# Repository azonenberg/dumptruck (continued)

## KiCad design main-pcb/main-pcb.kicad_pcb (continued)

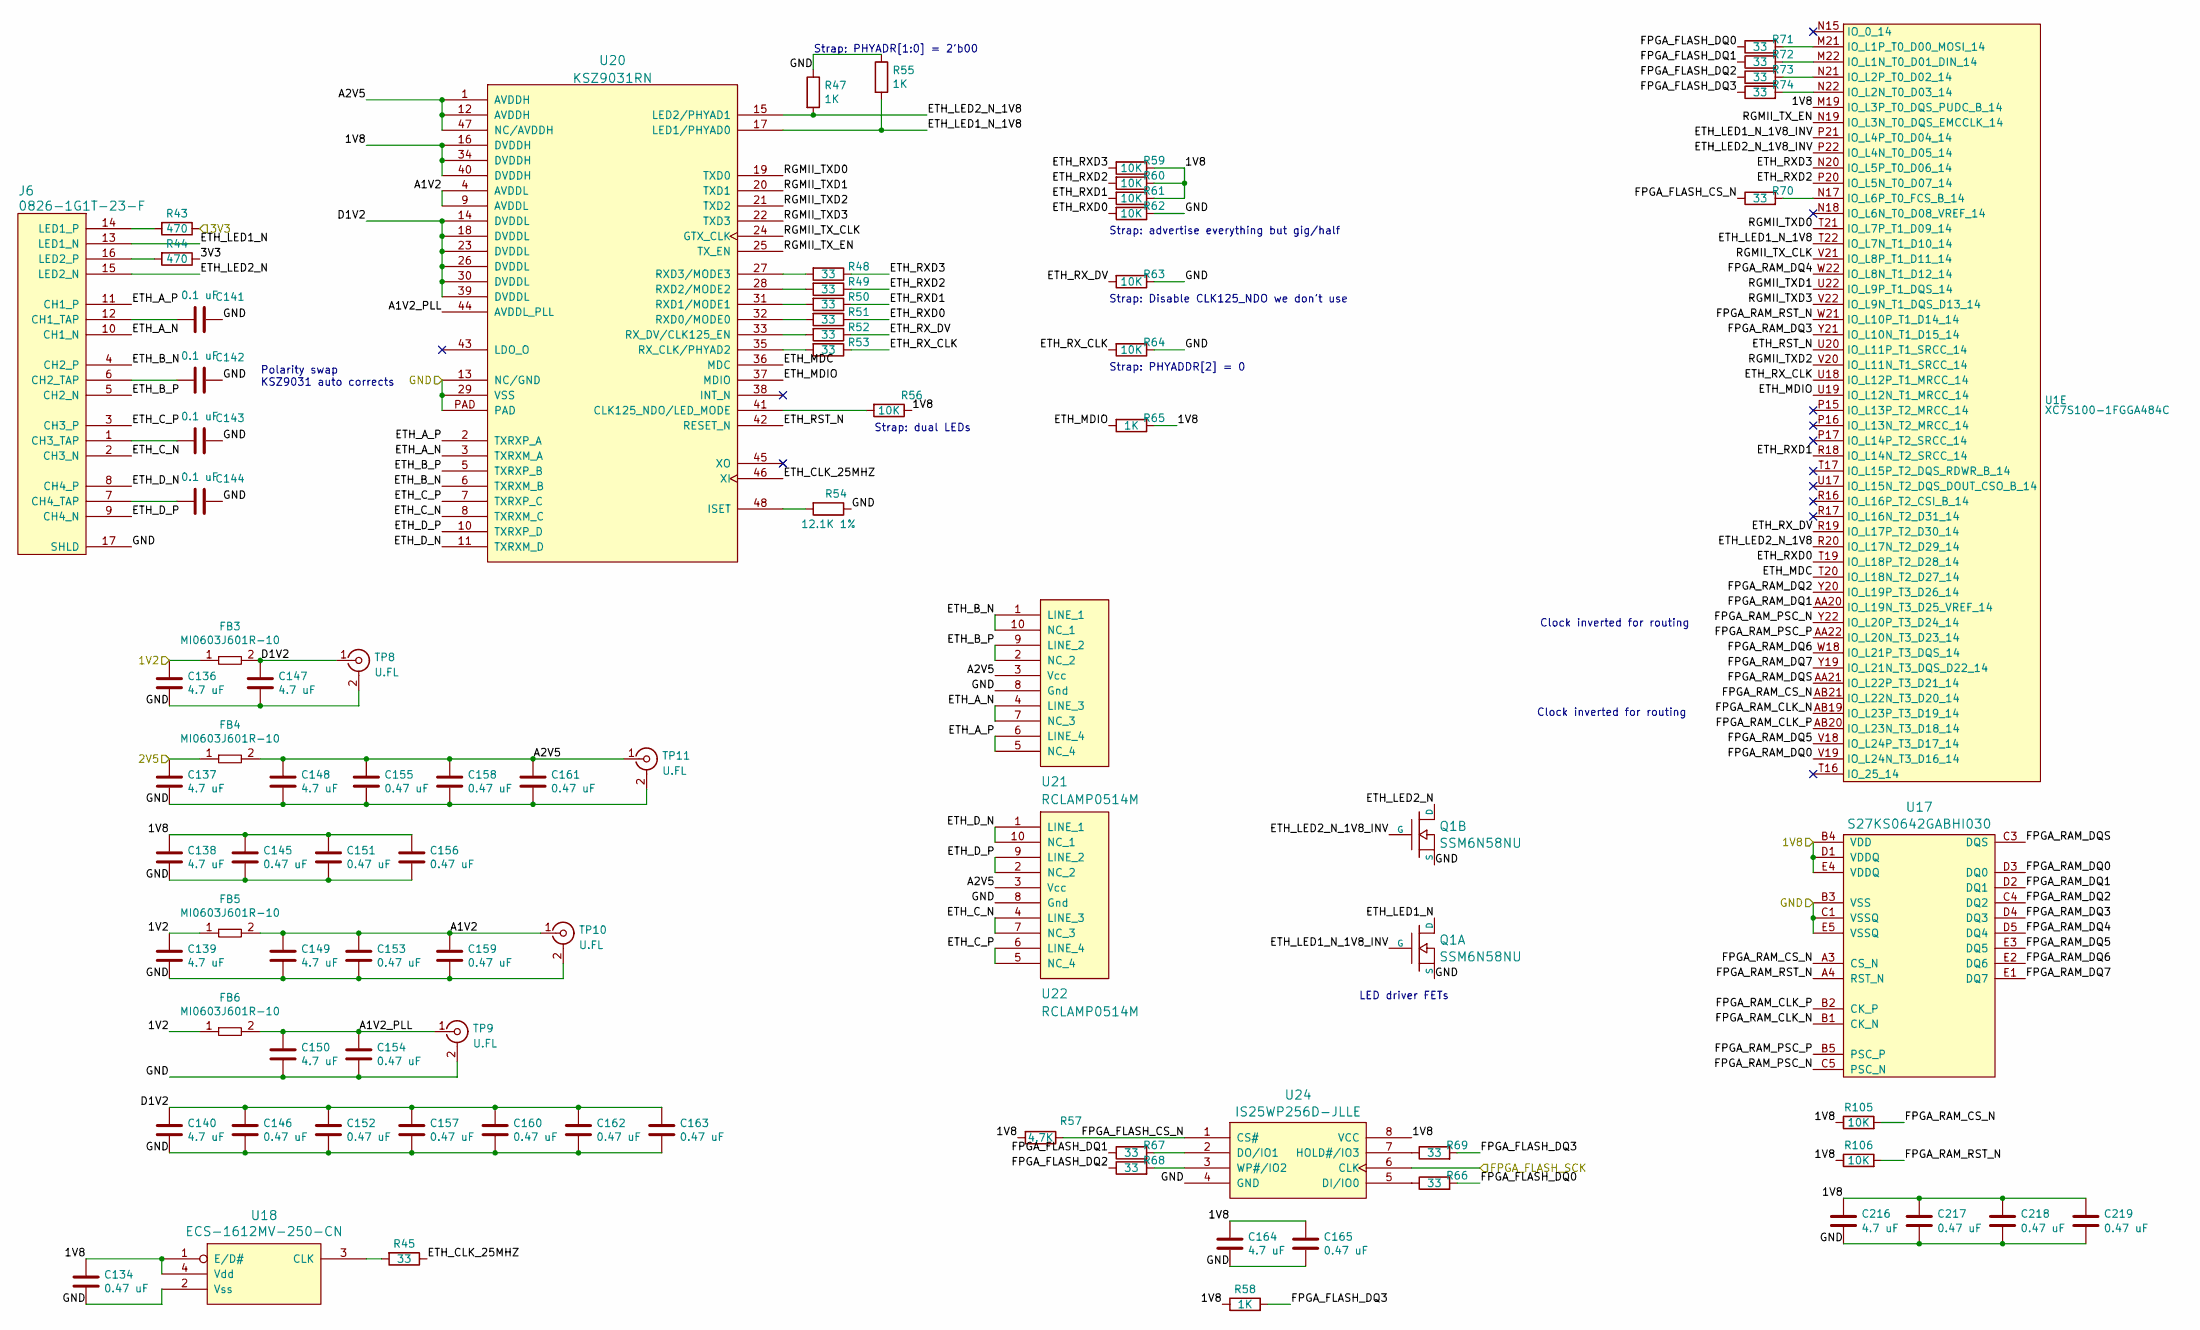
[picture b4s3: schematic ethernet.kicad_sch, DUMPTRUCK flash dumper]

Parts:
C134, C145, C146, C151, C152, C153, C154, C155, C156, C157, C158, C159, C160, C161, C162, C163, C165, C217, C218, C219: 0.47 uF; EIA_0402_CAP_NOSILK
C136, C137, C138, C139, C140, C147, C148, C149, C150, C164, C216: 4.7 uF; EIA_0603_CAP_NOSILK
C141, C142, C143, C144: 0.1 uF; EIA_0402_CAP_NOSILK
FB3, FB4, FB5, FB6: MI0603J601R-10; EIA_0603_INDUCTOR_NOSILK
J6: 0826-1G1T-23-F; CONN_BELFUSE_0826_1G1T_23_F
Q1: SSM6N58NU; DFN_6_0.65MM_2x2MM_GDS
R43, R44: 470; EIA_0402_RES_NOSILK
R45, R48, R49, R50, R51, R52, R53, R66, R67, R68, R69, R70, R71, R72, R73, R74: 33; EIA_0402_RES_NOSILK
R47, R55, R58, R65: 1K; EIA_0402_RES_NOSILK
R54: 12.1K 1%; EIA_0402_RES_NOSILK
R56, R59, R60, R61, R62, R63, R64, R105, R106: 10K; EIA_0402_RES_NOSILK
R57: 4.7K; EIA_0402_RES_NOSILK
TP8, TP9, TP10, TP11: U.FL; CONN_U.FL_TE_1909763-1
U1: XC7S100-1FGGA484C; BGA_484_22x22_FULLARRAY_1MM
U17: S27KS0642GABHI030; BGA_24_6x8_DEPOP1_1MM
U18: ECS-1612MV-250-CN; OSCILLATOR_1.6x1.2
U20: KSZ9031RN; QFN_48_0.5MM_7x7MM
U21, U22: RCLAMP0514M; SOP_10_0.5MM_3MM
U24: IS25WP256D-JLLE; DFN_8_1.27MM_8x6MM

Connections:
/1V2: C136.1, C139.1, FB3.1, FB5.1, FB6.1; also elsewhere on the board
/1V8: C134.1, C138.1, C145.1, C151.1, C156.1, C164.1, C165.1, C216.1, C217.1, C218.1, C219.1, R56.1, R57.2, R58.1, R59.1, R60.1, R61.1, R65.1, R105.1, R106.1, U1.M19 (IO_L3P_T0_DQS_PUDC_B_14), U17.B4 (VDD), U17.D1 (VDDQ), U17.E4 (VDDQ), U18.1 (E/D#), U18.4 (Vdd), U20.16 (DVDDH), U20.34 (DVDDH), U20.40 (DVDDH), U24.8 (VCC); also elsewhere on the board
/2V5: C137.1, FB4.1; also elsewhere on the board
/3V3: R43.1, R44.1; also elsewhere on the board
/Ethernet/A1V2: C149.1, C153.1, C159.1, FB5.2, TP10.1 (In), U20.4 (AVDDL), U20.9 (AVDDL)
/Ethernet/A1V2_PLL: C150.1, C154.1, FB6.2, TP9.1 (In), U20.44 (AVDDL_PLL)
/Ethernet/A2V5: C148.1, C155.1, C158.1, C161.1, FB4.2, TP11.1 (In), U20.1 (AVDDH), U20.12 (AVDDH), U20.47 (NC/AVDDH), U21.3 (Vcc), U22.3 (Vcc)
/Ethernet/D1V2: C140.1, C146.1, C147.1, C152.1, C157.1, C160.1, C162.1, C163.1, FB3.2, TP8.1 (In), U20.14 (DVDDL), U20.18 (DVDDL), U20.23 (DVDDL), U20.26 (DVDDL), U20.30 (DVDDL), U20.39 (DVDDL)
/Ethernet/ETH_A_N: J6.10 (CH1_N), U20.3 (TXRXM_A), U21.4 (LINE_3), U21.7 (NC_3)
/Ethernet/ETH_A_P: J6.11 (CH1_P), U20.2 (TXRXP_A), U21.5 (NC_4), U21.6 (LINE_4)
/Ethernet/ETH_B_N: J6.4 (CH2_P), U20.6 (TXRXM_B), U21.1 (LINE_1), U21.10 (NC_1)
/Ethernet/ETH_B_P: J6.5 (CH2_N), U20.5 (TXRXP_B), U21.2 (NC_2), U21.9 (LINE_2)
/Ethernet/ETH_CLK_25MHZ: R45.1, U20.46 (XI)
/Ethernet/ETH_C_N: J6.2 (CH3_N), U20.8 (TXRXM_C), U22.4 (LINE_3), U22.7 (NC_3)
/Ethernet/ETH_C_P: J6.3 (CH3_P), U20.7 (TXRXP_C), U22.5 (NC_4), U22.6 (LINE_4)
/Ethernet/ETH_D_N: J6.8 (CH4_P), U20.11 (TXRXM_D), U22.1 (LINE_1), U22.10 (NC_1)
/Ethernet/ETH_D_P: J6.9 (CH4_N), U20.10 (TXRXP_D), U22.2 (NC_2), U22.9 (LINE_2)
/Ethernet/ETH_LED1_N: J6.13 (LED1_N), Q1.D1 (D)
/Ethernet/ETH_LED1_N_1V8: R55.2, U1.T22 (IO_L7N_T1_D10_14), U20.17 (LED1/PHYAD0)
/Ethernet/ETH_LED1_N_1V8_INV: Q1.G1 (G), U1.P21 (IO_L4P_T0_D04_14)
/Ethernet/ETH_LED2_N: J6.15 (LED2_N), Q1.D2 (D)
/Ethernet/ETH_LED2_N_1V8: R47.2, U1.R20 (IO_L17N_T2_D29_14), U20.15 (LED2/PHYAD1)
/Ethernet/ETH_LED2_N_1V8_INV: Q1.G2 (G), U1.P22 (IO_L4N_T0_D05_14)
/Ethernet/ETH_MDC: U1.T20 (IO_L18N_T2_D27_14), U20.36 (MDC)
/Ethernet/ETH_MDIO: R65.2, U1.U19 (IO_L12N_T1_MRCC_14), U20.37 (MDIO)
/Ethernet/ETH_RST_N: U1.U20 (IO_L11P_T1_SRCC_14), U20.42 (RESET_N)
/Ethernet/ETH_RXD0: R51.1, R62.2, U1.T19 (IO_L18P_T2_D28_14)
/Ethernet/ETH_RXD1: R50.1, R61.2, U1.R18 (IO_L14N_T2_SRCC_14)
/Ethernet/ETH_RXD2: R49.1, R60.2, U1.P20 (IO_L5N_T0_D07_14)
/Ethernet/ETH_RXD3: R48.1, R59.2, U1.N20 (IO_L5P_T0_D06_14)
/Ethernet/ETH_RX_CLK: R53.1, R64.2, U1.U18 (IO_L12P_T1_MRCC_14)
/Ethernet/ETH_RX_DV: R52.1, R63.2, U1.R19 (IO_L17P_T2_D30_14)
/Ethernet/FPGA_FLASH_CS_N: R57.1, R70.1, U24.1 (CS#)
/Ethernet/FPGA_FLASH_DQ0: R66.2, R71.1
/Ethernet/FPGA_FLASH_DQ1: R67.1, R72.1
/Ethernet/FPGA_FLASH_DQ2: R68.1, R73.1
/Ethernet/FPGA_FLASH_DQ3: R58.2, R69.2, R74.1
/Ethernet/FPGA_RAM_CLK_N: U1.AB19 (IO_L23P_T3_D19_14), U17.B1 (CK_N)
/Ethernet/FPGA_RAM_CLK_P: U1.AB20 (IO_L23N_T3_D18_14), U17.B2 (CK_P)
/Ethernet/FPGA_RAM_CS_N: R105.2, U1.AB21 (IO_L22N_T3_D20_14), U17.A3 (CS_N)
/Ethernet/FPGA_RAM_DQ0: U1.V19 (IO_L24N_T3_D16_14), U17.D3 (DQ0)
/Ethernet/FPGA_RAM_DQ1: U1.AA20 (IO_L19N_T3_D25_VREF_14), U17.D2 (DQ1)
/Ethernet/FPGA_RAM_DQ2: U1.Y20 (IO_L19P_T3_D26_14), U17.C4 (DQ2)
/Ethernet/FPGA_RAM_DQ3: U1.Y21 (IO_L10N_T1_D15_14), U17.D4 (DQ3)
/Ethernet/FPGA_RAM_DQ4: U1.W22 (IO_L8N_T1_D12_14), U17.D5 (DQ4)
/Ethernet/FPGA_RAM_DQ5: U1.V18 (IO_L24P_T3_D17_14), U17.E3 (DQ5)
/Ethernet/FPGA_RAM_DQ6: U1.W18 (IO_L21P_T3_DQS_14), U17.E2 (DQ6)
/Ethernet/FPGA_RAM_DQ7: U1.Y19 (IO_L21N_T3_DQS_D22_14), U17.E1 (DQ7)
/Ethernet/FPGA_RAM_DQS: U1.AA21 (IO_L22P_T3_D21_14), U17.C3 (DQS)
/Ethernet/FPGA_RAM_PSC_N: U1.Y22 (IO_L20P_T3_D24_14), U17.C5 (PSC_N)
/Ethernet/FPGA_RAM_PSC_P: U1.AA22 (IO_L20N_T3_D23_14), U17.B5 (PSC_P)
/Ethernet/FPGA_RAM_RST_N: R106.2, U1.W21 (IO_L10P_T1_D14_14), U17.A4 (RST_N)
/Ethernet/RGMII_TXD0: U1.T21 (IO_L7P_T1_D09_14), U20.19 (TXD0)
/Ethernet/RGMII_TXD1: U1.U22 (IO_L9P_T1_DQS_14), U20.20 (TXD1)
/Ethernet/RGMII_TXD2: U1.V20 (IO_L11N_T1_SRCC_14), U20.21 (TXD2)
/Ethernet/RGMII_TXD3: U1.V22 (IO_L9N_T1_DQS_D13_14), U20.22 (TXD3)
/Ethernet/RGMII_TX_CLK: U1.V21 (IO_L8P_T1_D11_14), U20.24 (GTX_CLK)
/Ethernet/RGMII_TX_EN: U1.N19 (IO_L3N_T0_DQS_EMCCLK_14), U20.25 (TX_EN)
/FLASH_SCK: U24.6 (CLK); also elsewhere on the board
/GND: C134.2, C136.2, C137.2, C138.2, C139.2, C140.2, C141.1, C142.1, C143.1, C144.1, C145.2, C146.2, C147.2, C148.2, C149.2, C150.2, C151.2, C152.2, C153.2, C154.2, C155.2, C156.2, C157.2, C158.2, C159.2, C160.2, C161.2, C162.2, C163.2, C164.2, C165.2, C216.2, C217.2, C218.2, C219.2, J6.17 (SHLD), Q1.S1 (S), Q1.S2 (S), R47.1, R54.1, R55.1, R62.1, R63.1, R64.1, TP8.2 (Ext), TP9.2 (Ext), TP10.2 (Ext), TP11.2 (Ext), U17.B3 (VSS), U17.C1 (VSSQ), U17.E5 (VSSQ), U18.2 (Vss), U20.13 (NC/GND), U20.29 (VSS), U20.PAD, U21.8 (Gnd), U22.8 (Gnd), U24.4 (GND); also elsewhere on the board
unnamed: C141.2, J6.12 (CH1_TAP)
unnamed: C142.2, J6.6 (CH2_TAP)
unnamed: C143.2, J6.1 (CH3_TAP)
unnamed: C144.2, J6.7 (CH4_TAP)
unnamed: J6.14 (LED1_P), R43.2
unnamed: J6.16 (LED2_P), R44.2
unnamed: R72.2, U1.M22 (IO_L1N_T0_D01_DIN_14)
unnamed: R71.2, U1.M21 (IO_L1P_T0_D00_MOSI_14)
unnamed: R74.2, U1.N22 (IO_L2N_T0_D03_14)
unnamed: R73.2, U1.N21 (IO_L2P_T0_D02_14)
unnamed: R70.2, U1.N17 (IO_L6P_T0_FCS_B_14)
unnamed: R45.2, U18.3 (CLK)
unnamed: R56.2, U20.41 (CLK125_NDO/LED_MODE)
unnamed: R54.2, U20.48 (ISET)
unnamed: R51.2, U20.32 (RXD0/MODE0)
unnamed: R50.2, U20.31 (RXD1/MODE1)
unnamed: R49.2, U20.28 (RXD2/MODE2)
unnamed: R48.2, U20.27 (RXD3/MODE3)
unnamed: R53.2, U20.35 (RX_CLK/PHYAD2)
unnamed: R52.2, U20.33 (RX_DV/CLK125_EN)
unnamed: R66.1, U24.5 (DI/IO0)
unnamed: R67.2, U24.2 (DO/IO1)
unnamed: R69.1, U24.7 (HOLD#/IO3)
unnamed: R68.2, U24.3 (WP#/IO2)

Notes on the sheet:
Strap: Disable CLK125_NDO we don't use
Strap: dual LEDs
Strap: PHYADDR[2] = 0
LED driver FETs
Polarity swap KSZ9031 auto corrects
Strap: advertise everything but gig/half
Clock inverted for routing
Strap: PHYADR[1:0] = 2'b00

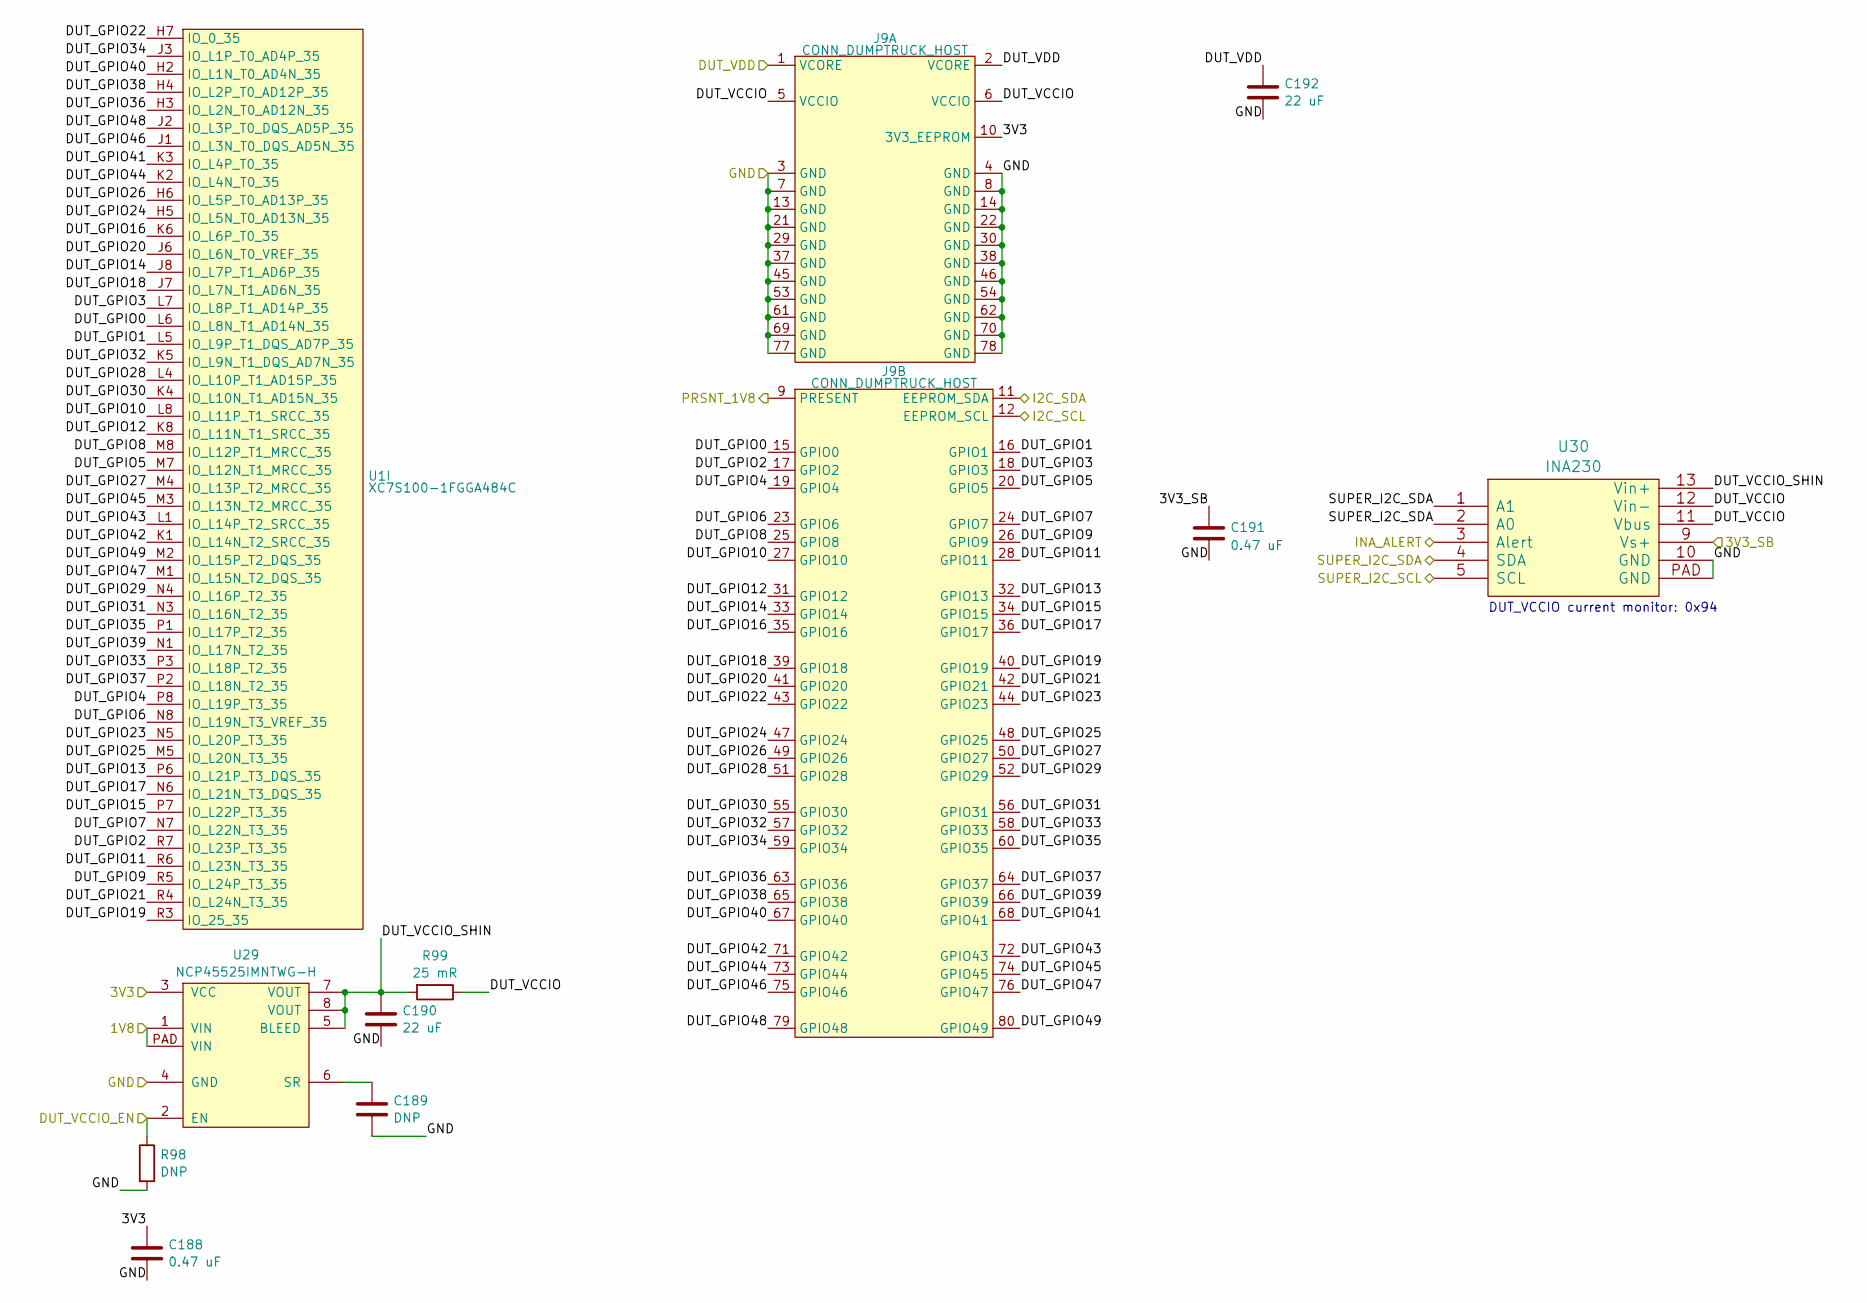
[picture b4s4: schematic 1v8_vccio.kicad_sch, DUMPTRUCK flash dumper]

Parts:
C188, C191: 0.47 uF; EIA_0402_CAP_NOSILK
C189: DNP; EIA_0402_CAP_NOSILK
C190: 22 uF; EIA_0805_CAP_NOSILK
C192: 22 uF; EIA_1206_CAP_NOSILK
J9: CONN_DUMPTRUCK_HOST; CONN_SAMTEC_BTE-040-01-F-D-A-K
R98: DNP; EIA_0402_RES_NOSILK
R99: 25 mR; EIA_0402_RES_NOSILK
U1: XC7S100-1FGGA484C; BGA_484_22x22_FULLARRAY_1MM
U29: NCP45525IMNTWG-H; DFN_8_0.5MM_2x2MM
U30: INA230; QFN_16_0.5MM_3x3MM

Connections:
/1V8: U29.1 (VIN), U29.PAD (VIN); also elsewhere on the board
/1V8 VCCIO socket/DUT_GPIO0: J9.15 (GPIO0), U1.L6 (IO_L8N_T1_AD14N_35)
/1V8 VCCIO socket/DUT_GPIO1: J9.16 (GPIO1), U1.L5 (IO_L9P_T1_DQS_AD7P_35)
/1V8 VCCIO socket/DUT_GPIO2: J9.17 (GPIO2), U1.R7 (IO_L23P_T3_35)
/1V8 VCCIO socket/DUT_GPIO3: J9.18 (GPIO3), U1.L7 (IO_L8P_T1_AD14P_35)
/1V8 VCCIO socket/DUT_GPIO4: J9.19 (GPIO4), U1.P8 (IO_L19P_T3_35)
/1V8 VCCIO socket/DUT_GPIO5: J9.20 (GPIO5), U1.M7 (IO_L12N_T1_MRCC_35)
/1V8 VCCIO socket/DUT_GPIO6: J9.23 (GPIO6), U1.N8 (IO_L19N_T3_VREF_35)
/1V8 VCCIO socket/DUT_GPIO7: J9.24 (GPIO7), U1.N7 (IO_L22N_T3_35)
/1V8 VCCIO socket/DUT_GPIO8: J9.25 (GPIO8), U1.M8 (IO_L12P_T1_MRCC_35)
/1V8 VCCIO socket/DUT_GPIO9: J9.26 (GPIO9), U1.R5 (IO_L24P_T3_35)
/1V8 VCCIO socket/DUT_GPIO10: J9.27 (GPIO10), U1.L8 (IO_L11P_T1_SRCC_35)
/1V8 VCCIO socket/DUT_GPIO11: J9.28 (GPIO11), U1.R6 (IO_L23N_T3_35)
/1V8 VCCIO socket/DUT_GPIO12: J9.31 (GPIO12), U1.K8 (IO_L11N_T1_SRCC_35)
/1V8 VCCIO socket/DUT_GPIO13: J9.32 (GPIO13), U1.P6 (IO_L21P_T3_DQS_35)
/1V8 VCCIO socket/DUT_GPIO14: J9.33 (GPIO14), U1.J8 (IO_L7P_T1_AD6P_35)
/1V8 VCCIO socket/DUT_GPIO15: J9.34 (GPIO15), U1.P7 (IO_L22P_T3_35)
/1V8 VCCIO socket/DUT_GPIO16: J9.35 (GPIO16), U1.K6 (IO_L6P_T0_35)
/1V8 VCCIO socket/DUT_GPIO17: J9.36 (GPIO17), U1.N6 (IO_L21N_T3_DQS_35)
/1V8 VCCIO socket/DUT_GPIO18: J9.39 (GPIO18), U1.J7 (IO_L7N_T1_AD6N_35)
/1V8 VCCIO socket/DUT_GPIO19: J9.40 (GPIO19), U1.R3 (IO_25_35)
/1V8 VCCIO socket/DUT_GPIO20: J9.41 (GPIO20), U1.J6 (IO_L6N_T0_VREF_35)
/1V8 VCCIO socket/DUT_GPIO21: J9.42 (GPIO21), U1.R4 (IO_L24N_T3_35)
/1V8 VCCIO socket/DUT_GPIO22: J9.43 (GPIO22), U1.H7 (IO_0_35)
/1V8 VCCIO socket/DUT_GPIO23: J9.44 (GPIO23), U1.N5 (IO_L20P_T3_35)
/1V8 VCCIO socket/DUT_GPIO24: J9.47 (GPIO24), U1.H5 (IO_L5N_T0_AD13N_35)
/1V8 VCCIO socket/DUT_GPIO25: J9.48 (GPIO25), U1.M5 (IO_L20N_T3_35)
/1V8 VCCIO socket/DUT_GPIO26: J9.49 (GPIO26), U1.H6 (IO_L5P_T0_AD13P_35)
/1V8 VCCIO socket/DUT_GPIO27: J9.50 (GPIO27), U1.M4 (IO_L13P_T2_MRCC_35)
/1V8 VCCIO socket/DUT_GPIO28: J9.51 (GPIO28), U1.L4 (IO_L10P_T1_AD15P_35)
/1V8 VCCIO socket/DUT_GPIO29: J9.52 (GPIO29), U1.N4 (IO_L16P_T2_35)
/1V8 VCCIO socket/DUT_GPIO30: J9.55 (GPIO30), U1.K4 (IO_L10N_T1_AD15N_35)
/1V8 VCCIO socket/DUT_GPIO31: J9.56 (GPIO31), U1.N3 (IO_L16N_T2_35)
/1V8 VCCIO socket/DUT_GPIO32: J9.57 (GPIO32), U1.K5 (IO_L9N_T1_DQS_AD7N_35)
/1V8 VCCIO socket/DUT_GPIO33: J9.58 (GPIO33), U1.P3 (IO_L18P_T2_35)
/1V8 VCCIO socket/DUT_GPIO34: J9.59 (GPIO34), U1.J3 (IO_L1P_T0_AD4P_35)
/1V8 VCCIO socket/DUT_GPIO35: J9.60 (GPIO35), U1.P1 (IO_L17P_T2_35)
/1V8 VCCIO socket/DUT_GPIO36: J9.63 (GPIO36), U1.H3 (IO_L2N_T0_AD12N_35)
/1V8 VCCIO socket/DUT_GPIO37: J9.64 (GPIO37), U1.P2 (IO_L18N_T2_35)
/1V8 VCCIO socket/DUT_GPIO38: J9.65 (GPIO38), U1.H4 (IO_L2P_T0_AD12P_35)
/1V8 VCCIO socket/DUT_GPIO39: J9.66 (GPIO39), U1.N1 (IO_L17N_T2_35)
/1V8 VCCIO socket/DUT_GPIO40: J9.67 (GPIO40), U1.H2 (IO_L1N_T0_AD4N_35)
/1V8 VCCIO socket/DUT_GPIO41: J9.68 (GPIO41), U1.K3 (IO_L4P_T0_35)
/1V8 VCCIO socket/DUT_GPIO42: J9.71 (GPIO42), U1.K1 (IO_L14N_T2_SRCC_35)
/1V8 VCCIO socket/DUT_GPIO43: J9.72 (GPIO43), U1.L1 (IO_L14P_T2_SRCC_35)
/1V8 VCCIO socket/DUT_GPIO44: J9.73 (GPIO44), U1.K2 (IO_L4N_T0_35)
/1V8 VCCIO socket/DUT_GPIO45: J9.74 (GPIO45), U1.M3 (IO_L13N_T2_MRCC_35)
/1V8 VCCIO socket/DUT_GPIO46: J9.75 (GPIO46), U1.J1 (IO_L3N_T0_DQS_AD5N_35)
/1V8 VCCIO socket/DUT_GPIO47: J9.76 (GPIO47), U1.M1 (IO_L15N_T2_DQS_35)
/1V8 VCCIO socket/DUT_GPIO48: J9.79 (GPIO48), U1.J2 (IO_L3P_T0_DQS_AD5P_35)
/1V8 VCCIO socket/DUT_GPIO49: J9.80 (GPIO49), U1.M2 (IO_L15P_T2_DQS_35)
/1V8 VCCIO socket/DUT_VCCIO: J9.5 (VCCIO), J9.6 (VCCIO), R99.1, U30.11 (Vbus), U30.12 (Vin-)
/1V8 VCCIO socket/DUT_VCCIO_SHIN: C190.1, R99.2, U29.5 (BLEED), U29.7 (VOUT), U29.8 (VOUT), U30.13 (Vin+)
/3V3: C188.1, J9.10 (3V3_EEPROM), U29.3 (VCC); also elsewhere on the board
/3V3_SB: C191.1, U30.9 (Vs+); also elsewhere on the board
/DUT_VCCIO_EN: R98.1, U29.2 (EN); also elsewhere on the board
/DUT_VDD: C192.1, J9.1 (VCORE), J9.2 (VCORE); also elsewhere on the board
/GND: C188.2, C189.2, C190.2, C191.2, C192.2, J9.3 (GND), J9.4 (GND), J9.7 (GND), J9.8 (GND), J9.13 (GND), J9.14 (GND), J9.21 (GND), J9.22 (GND), J9.29 (GND), J9.30 (GND), J9.37 (GND), J9.38 (GND), J9.45 (GND), J9.46 (GND), J9.53 (GND), J9.54 (GND), J9.61 (GND), J9.62 (GND), J9.69 (GND), J9.70 (GND), J9.77 (GND), J9.78 (GND), R98.2, U29.4 (GND), U30.10 (GND), U30.PAD (GND); also elsewhere on the board
/I2C_SCL: J9.12 (EEPROM_SCL); also elsewhere on the board
/I2C_SDA: J9.11 (EEPROM_SDA); also elsewhere on the board
/INA_ALERT: U30.3 (Alert); also elsewhere on the board
/PRSNT_1V8: J9.9 (PRESENT); also elsewhere on the board
/SUPER_I2C_SCL: U30.5 (SCL); also elsewhere on the board
/SUPER_I2C_SDA: U30.1 (A1), U30.2 (A0), U30.4 (SDA); also elsewhere on the board
unnamed: C189.1, U29.6 (SR)

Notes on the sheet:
DUT_VCCIO current monitor: 0x94

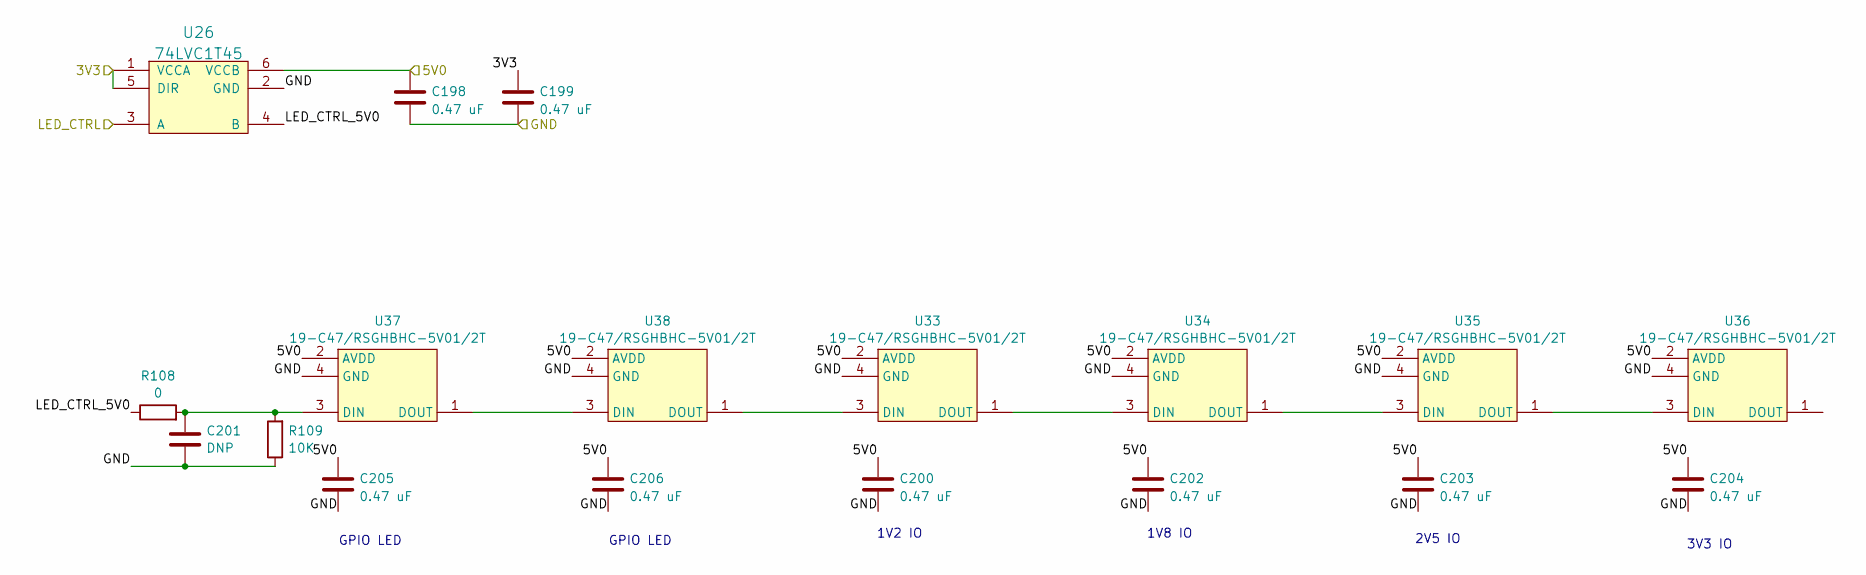
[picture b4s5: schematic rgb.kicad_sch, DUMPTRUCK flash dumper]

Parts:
C198, C199, C200, C202, C203, C204, C205, C206: 0.47 uF; EIA_0402_CAP_NOSILK
C201: DNP; EIA_0402_CAP_NOSILK
R108: 0; EIA_0402_RES_NOSILK
R109: 10K; EIA_0402_RES_NOSILK
U26: 74LVC1T45; DFN_6_0.5MM_1.6x1.6MM_TI_DPK
U33, U34, U35, U36, U37, U38: 19-C47/RSGHBHC-5V01/2T; LED_EVERLIGHT_19-C47_RSGHBHC-5V01_2T

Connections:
/3V3: C199.1, U26.1 (VCCA), U26.5 (DIR); also elsewhere on the board
/GND: C198.2, C199.2, C200.2, C201.2, C202.2, C203.2, C204.2, C205.2, C206.2, R109.1, U26.2 (GND), U33.4 (GND), U34.4 (GND), U35.4 (GND), U36.4 (GND), U37.4 (GND), U38.4 (GND); also elsewhere on the board
/LED_CTRL: U26.3 (A); also elsewhere on the board
/RGB LEDs/LED_CTRL_5V0: R108.1, U26.4 (B)
/VBUS_SHOUT: C198.1, C200.1, C202.1, C203.1, C204.1, C205.1, C206.1, U26.6 (VCCB), U33.2 (AVDD), U34.2 (AVDD), U35.2 (AVDD), U36.2 (AVDD), U37.2 (AVDD), U38.2 (AVDD); also elsewhere on the board
unnamed: U33.3 (DIN), U38.1 (DOUT)
unnamed: U33.1 (DOUT), U34.3 (DIN)
unnamed: U34.1 (DOUT), U35.3 (DIN)
unnamed: U35.1 (DOUT), U36.3 (DIN)
unnamed: C201.1, R108.2, R109.2, U37.3 (DIN)
unnamed: U37.1 (DOUT), U38.3 (DIN)

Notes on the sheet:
1V2 IO
GPIO LED
2V5 IO
1V8 IO
3V3 IO

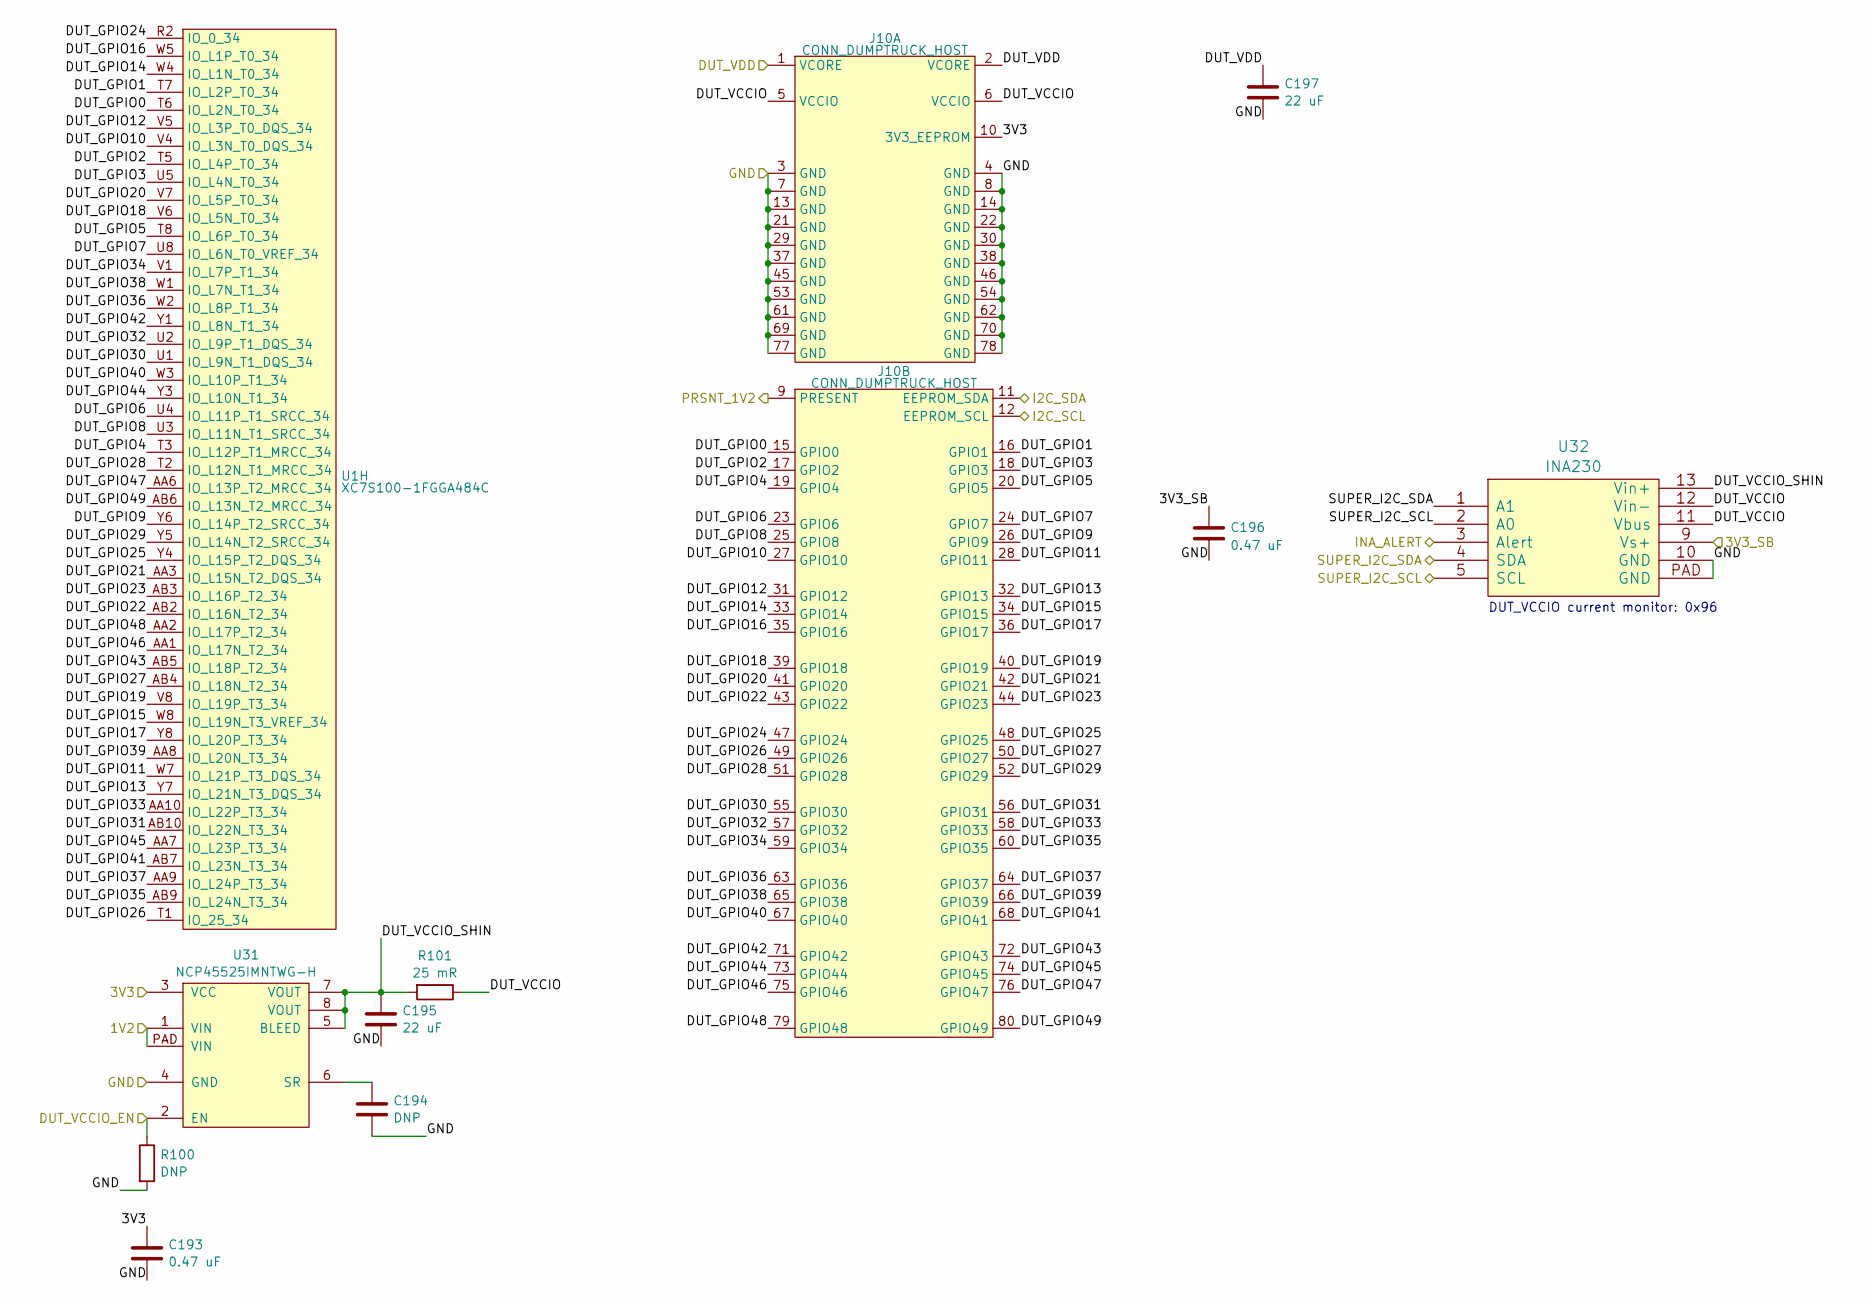
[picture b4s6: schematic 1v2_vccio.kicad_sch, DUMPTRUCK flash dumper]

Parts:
C193, C196: 0.47 uF; EIA_0402_CAP_NOSILK
C194: DNP; EIA_0402_CAP_NOSILK
C195: 22 uF; EIA_0805_CAP_NOSILK
C197: 22 uF; EIA_1206_CAP_NOSILK
J10: CONN_DUMPTRUCK_HOST; CONN_SAMTEC_BTE-040-01-F-D-A-K
R100: DNP; EIA_0402_RES_NOSILK
R101: 25 mR; EIA_0402_RES_NOSILK
U1: XC7S100-1FGGA484C; BGA_484_22x22_FULLARRAY_1MM
U31: NCP45525IMNTWG-H; DFN_8_0.5MM_2x2MM
U32: INA230; QFN_16_0.5MM_3x3MM

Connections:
/1V2: U31.1 (VIN), U31.PAD (VIN); also elsewhere on the board
/1V2 VCCIO socket/DUT_GPIO0: J10.15 (GPIO0), U1.T6 (IO_L2N_T0_34)
/1V2 VCCIO socket/DUT_GPIO1: J10.16 (GPIO1), U1.T7 (IO_L2P_T0_34)
/1V2 VCCIO socket/DUT_GPIO2: J10.17 (GPIO2), U1.T5 (IO_L4P_T0_34)
/1V2 VCCIO socket/DUT_GPIO3: J10.18 (GPIO3), U1.U5 (IO_L4N_T0_34)
/1V2 VCCIO socket/DUT_GPIO4: J10.19 (GPIO4), U1.T3 (IO_L12P_T1_MRCC_34)
/1V2 VCCIO socket/DUT_GPIO5: J10.20 (GPIO5), U1.T8 (IO_L6P_T0_34)
/1V2 VCCIO socket/DUT_GPIO6: J10.23 (GPIO6), U1.U4 (IO_L11P_T1_SRCC_34)
/1V2 VCCIO socket/DUT_GPIO7: J10.24 (GPIO7), U1.U8 (IO_L6N_T0_VREF_34)
/1V2 VCCIO socket/DUT_GPIO8: J10.25 (GPIO8), U1.U3 (IO_L11N_T1_SRCC_34)
/1V2 VCCIO socket/DUT_GPIO9: J10.26 (GPIO9), U1.Y6 (IO_L14P_T2_SRCC_34)
/1V2 VCCIO socket/DUT_GPIO10: J10.27 (GPIO10), U1.V4 (IO_L3N_T0_DQS_34)
/1V2 VCCIO socket/DUT_GPIO11: J10.28 (GPIO11), U1.W7 (IO_L21P_T3_DQS_34)
/1V2 VCCIO socket/DUT_GPIO12: J10.31 (GPIO12), U1.V5 (IO_L3P_T0_DQS_34)
/1V2 VCCIO socket/DUT_GPIO13: J10.32 (GPIO13), U1.Y7 (IO_L21N_T3_DQS_34)
/1V2 VCCIO socket/DUT_GPIO14: J10.33 (GPIO14), U1.W4 (IO_L1N_T0_34)
/1V2 VCCIO socket/DUT_GPIO15: J10.34 (GPIO15), U1.W8 (IO_L19N_T3_VREF_34)
/1V2 VCCIO socket/DUT_GPIO16: J10.35 (GPIO16), U1.W5 (IO_L1P_T0_34)
/1V2 VCCIO socket/DUT_GPIO17: J10.36 (GPIO17), U1.Y8 (IO_L20P_T3_34)
/1V2 VCCIO socket/DUT_GPIO18: J10.39 (GPIO18), U1.V6 (IO_L5N_T0_34)
/1V2 VCCIO socket/DUT_GPIO19: J10.40 (GPIO19), U1.V8 (IO_L19P_T3_34)
/1V2 VCCIO socket/DUT_GPIO20: J10.41 (GPIO20), U1.V7 (IO_L5P_T0_34)
/1V2 VCCIO socket/DUT_GPIO21: J10.42 (GPIO21), U1.AA3 (IO_L15N_T2_DQS_34)
/1V2 VCCIO socket/DUT_GPIO22: J10.43 (GPIO22), U1.AB2 (IO_L16N_T2_34)
/1V2 VCCIO socket/DUT_GPIO23: J10.44 (GPIO23), U1.AB3 (IO_L16P_T2_34)
/1V2 VCCIO socket/DUT_GPIO24: J10.47 (GPIO24), U1.R2 (IO_0_34)
/1V2 VCCIO socket/DUT_GPIO25: J10.48 (GPIO25), U1.Y4 (IO_L15P_T2_DQS_34)
/1V2 VCCIO socket/DUT_GPIO26: J10.49 (GPIO26), U1.T1 (IO_25_34)
/1V2 VCCIO socket/DUT_GPIO27: J10.50 (GPIO27), U1.AB4 (IO_L18N_T2_34)
/1V2 VCCIO socket/DUT_GPIO28: J10.51 (GPIO28), U1.T2 (IO_L12N_T1_MRCC_34)
/1V2 VCCIO socket/DUT_GPIO29: J10.52 (GPIO29), U1.Y5 (IO_L14N_T2_SRCC_34)
/1V2 VCCIO socket/DUT_GPIO30: J10.55 (GPIO30), U1.U1 (IO_L9N_T1_DQS_34)
/1V2 VCCIO socket/DUT_GPIO31: J10.56 (GPIO31), U1.AB10 (IO_L22N_T3_34)
/1V2 VCCIO socket/DUT_GPIO32: J10.57 (GPIO32), U1.U2 (IO_L9P_T1_DQS_34)
/1V2 VCCIO socket/DUT_GPIO33: J10.58 (GPIO33), U1.AA10 (IO_L22P_T3_34)
/1V2 VCCIO socket/DUT_GPIO34: J10.59 (GPIO34), U1.V1 (IO_L7P_T1_34)
/1V2 VCCIO socket/DUT_GPIO35: J10.60 (GPIO35), U1.AB9 (IO_L24N_T3_34)
/1V2 VCCIO socket/DUT_GPIO36: J10.63 (GPIO36), U1.W2 (IO_L8P_T1_34)
/1V2 VCCIO socket/DUT_GPIO37: J10.64 (GPIO37), U1.AA9 (IO_L24P_T3_34)
/1V2 VCCIO socket/DUT_GPIO38: J10.65 (GPIO38), U1.W1 (IO_L7N_T1_34)
/1V2 VCCIO socket/DUT_GPIO39: J10.66 (GPIO39), U1.AA8 (IO_L20N_T3_34)
/1V2 VCCIO socket/DUT_GPIO40: J10.67 (GPIO40), U1.W3 (IO_L10P_T1_34)
/1V2 VCCIO socket/DUT_GPIO41: J10.68 (GPIO41), U1.AB7 (IO_L23N_T3_34)
/1V2 VCCIO socket/DUT_GPIO42: J10.71 (GPIO42), U1.Y1 (IO_L8N_T1_34)
/1V2 VCCIO socket/DUT_GPIO43: J10.72 (GPIO43), U1.AB5 (IO_L18P_T2_34)
/1V2 VCCIO socket/DUT_GPIO44: J10.73 (GPIO44), U1.Y3 (IO_L10N_T1_34)
/1V2 VCCIO socket/DUT_GPIO45: J10.74 (GPIO45), U1.AA7 (IO_L23P_T3_34)
/1V2 VCCIO socket/DUT_GPIO46: J10.75 (GPIO46), U1.AA1 (IO_L17N_T2_34)
/1V2 VCCIO socket/DUT_GPIO47: J10.76 (GPIO47), U1.AA6 (IO_L13P_T2_MRCC_34)
/1V2 VCCIO socket/DUT_GPIO48: J10.79 (GPIO48), U1.AA2 (IO_L17P_T2_34)
/1V2 VCCIO socket/DUT_GPIO49: J10.80 (GPIO49), U1.AB6 (IO_L13N_T2_MRCC_34)
/1V2 VCCIO socket/DUT_VCCIO: J10.5 (VCCIO), J10.6 (VCCIO), R101.1, U32.11 (Vbus), U32.12 (Vin-)
/1V2 VCCIO socket/DUT_VCCIO_SHIN: C195.1, R101.2, U31.5 (BLEED), U31.7 (VOUT), U31.8 (VOUT), U32.13 (Vin+)
/3V3: C193.1, J10.10 (3V3_EEPROM), U31.3 (VCC); also elsewhere on the board
/3V3_SB: C196.1, U32.9 (Vs+); also elsewhere on the board
/DUT_VCCIO_EN: R100.1, U31.2 (EN); also elsewhere on the board
/DUT_VDD: C197.1, J10.1 (VCORE), J10.2 (VCORE); also elsewhere on the board
/GND: C193.2, C194.2, C195.2, C196.2, C197.2, J10.3 (GND), J10.4 (GND), J10.7 (GND), J10.8 (GND), J10.13 (GND), J10.14 (GND), J10.21 (GND), J10.22 (GND), J10.29 (GND), J10.30 (GND), J10.37 (GND), J10.38 (GND), J10.45 (GND), J10.46 (GND), J10.53 (GND), J10.54 (GND), J10.61 (GND), J10.62 (GND), J10.69 (GND), J10.70 (GND), J10.77 (GND), J10.78 (GND), R100.2, U31.4 (GND), U32.10 (GND), U32.PAD (GND); also elsewhere on the board
/I2C_SCL: J10.12 (EEPROM_SCL); also elsewhere on the board
/I2C_SDA: J10.11 (EEPROM_SDA); also elsewhere on the board
/INA_ALERT: U32.3 (Alert); also elsewhere on the board
/PRSNT_1V2: J10.9 (PRESENT); also elsewhere on the board
/SUPER_I2C_SCL: U32.2 (A0), U32.5 (SCL); also elsewhere on the board
/SUPER_I2C_SDA: U32.1 (A1), U32.4 (SDA); also elsewhere on the board
unnamed: C194.1, U31.6 (SR)

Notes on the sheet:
DUT_VCCIO current monitor: 0x96
